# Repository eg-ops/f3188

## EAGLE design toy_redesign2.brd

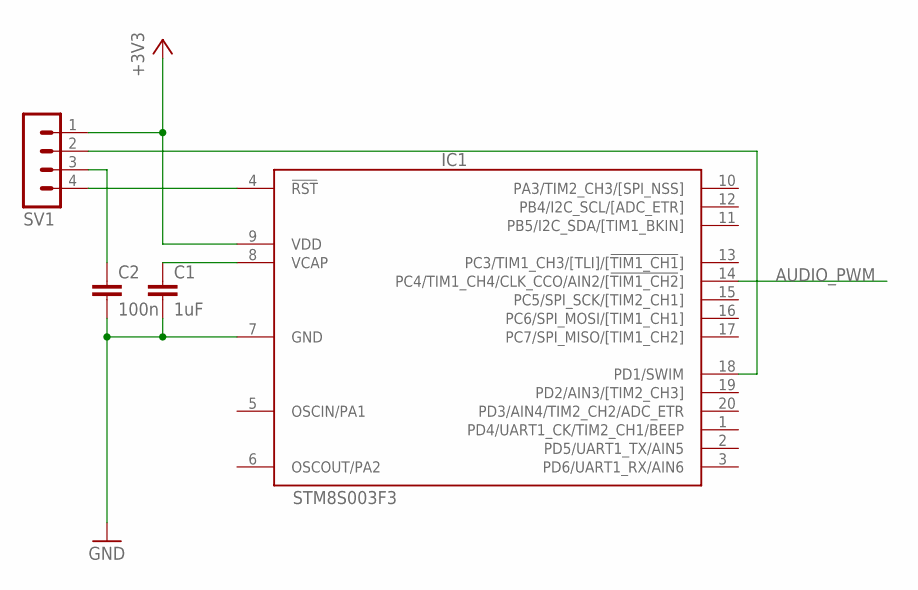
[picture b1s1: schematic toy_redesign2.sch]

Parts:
C1: 1uF; C0805
C2: 100n; C0805
IC1: STM8S003F3; TSSOP20
SV1: MA04-1

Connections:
+3V3: IC1.9 (VDD), SV1.1
AUDIO_PWM: IC1.14 (PC4/TIM1_CH4/CLK_CCO/AIN2/[!TIM1_CH2!])
GND: C1.2, C2.2, IC1.7 (GND)
unnamed: IC1.4 (!RST), SV1.4
unnamed: C1.1, IC1.8 (VCAP)
unnamed: C2.1, SV1.3
unnamed: IC1.18 (PD1/SWIM), SV1.2

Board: 2 copper layers, 4 parts (0 on the bottom side), 6 nets, no tracks yet.

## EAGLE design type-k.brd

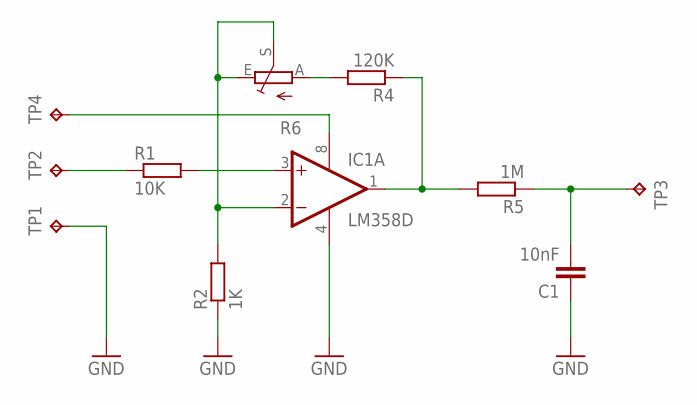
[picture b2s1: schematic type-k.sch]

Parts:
C1: 10nF; C0805
IC1: LM358D; SO08
R1: 10K; R0805
R2: 1K; R0805
R4: 120K; R0805
R5: 1M; R0805
R6: TRIM_EU-CA6V; CA6V
TP1, TP2, TP3, TP4: TPB2,54; B2,54

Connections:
GND: C1.1, IC1.4 (V-), R2.1, TP1.TP
unnamed: R1.1, TP2.TP
unnamed: IC1.3 (+IN), R1.2
unnamed: IC1.2 (-IN), R2.2, R6.E, R6.S
unnamed: R4.2, R6.A
unnamed: IC1.1 (OUT), R4.1, R5.2
unnamed: C1.2, R5.1, TP3.TP
unnamed: IC1.8 (V+), TP4.TP

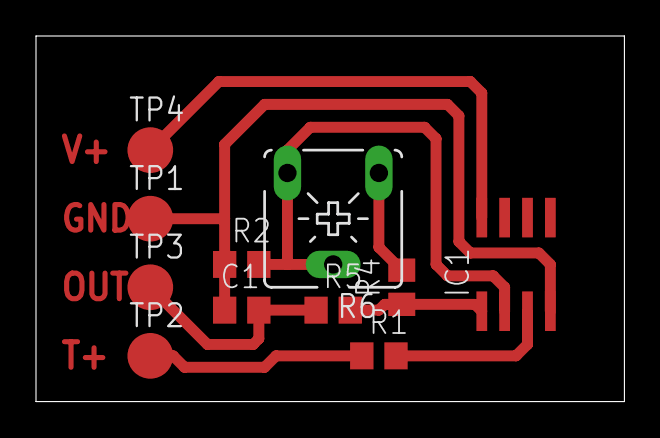
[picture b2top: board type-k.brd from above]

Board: 2 copper layers, 32.7 x 20.3 mm, 11 parts (0 on the bottom side), 8 nets.

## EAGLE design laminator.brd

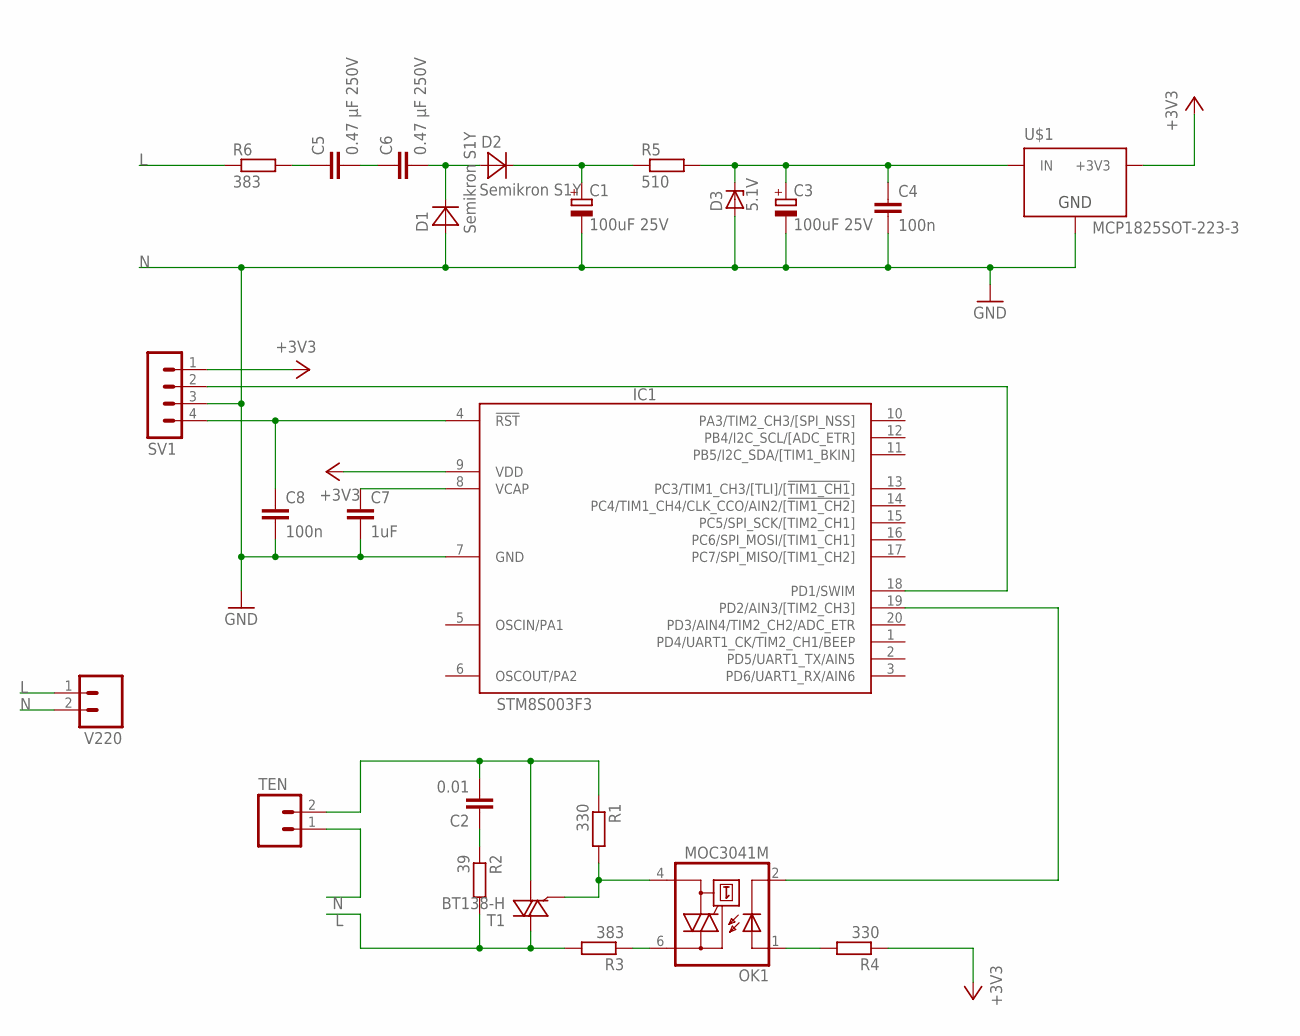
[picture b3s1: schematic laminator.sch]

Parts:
C1, C3: 100uF 25V; E2,5-6
C2: 0.01; C050-025X075
C4, C8: 100n; C0805
C5, C6: 0.47 µF 250V; C150-072X183
C7: 1uF; C0805
D1, D2: Semikron S1Y; SMA
D3: 5.1V; SMB
IC1: STM8S003F3; TSSOP20
OK1: MOC3041M; DIL06
R1: 330; 0207/7
R2: 39; 0207/7
R3, R6: 383; 0207/7
R4: 330; R1206
R5: 510; R0805
SV1: MA04-1
T1: BT138-H; TO220BH
TEN: M02; 02P
U$1: MCP1825SOT-223-3; SOT-223
V220: M02; 02P

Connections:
+3V3: IC1.9 (VDD), R4.1, SV1.1, U$1.3 (+3V3)
L: R2.2, R3.2, R6.1, T1.T2 (A2), V220.1
N: C1.-, C3.-, C4.2, C7.2, C8.2, D1.A, D3.A, IC1.7 (GND), SV1.3, TEN.1, U$1.2 (GND), V220.2
unnamed: OK1.6 (A2), R3.1
unnamed: C7.1, IC1.8 (VCAP)
unnamed: OK1.4 (A1), R1.2, T1.G
unnamed: C2.2, R1.1, T1.T1 (A1), TEN.2
unnamed: C6.2, D1.C, D2.A
unnamed: C2.1, R2.1
unnamed: C8.1, IC1.4 (!RST), SV1.4
unnamed: OK1.1 (A), R4.2
unnamed: IC1.18 (PD1/SWIM), SV1.2
unnamed: IC1.19 (PD2/AIN3/[TIM2_CH3]), OK1.2 (C)
unnamed: C1.+, D2.C, R5.1
unnamed: C3.+, C4.1, D3.C, R5.2, U$1.1 (IN)
unnamed: C5.1, R6.2
unnamed: C5.2, C6.1

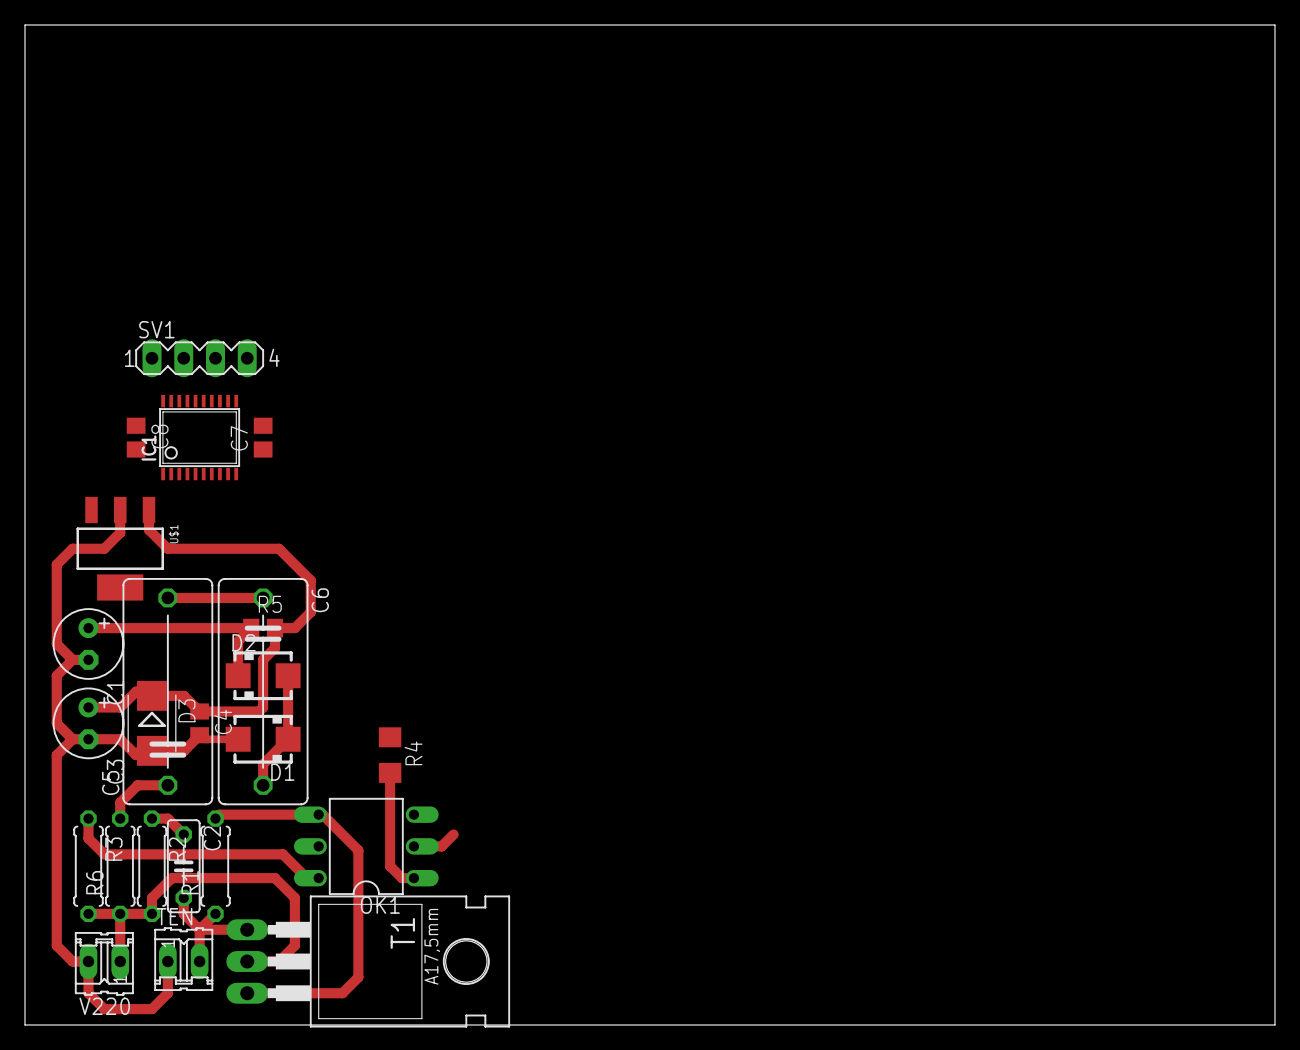
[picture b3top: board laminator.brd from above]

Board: 2 copper layers, 100.0 x 80.0 mm, 24 parts (0 on the bottom side), 17 nets.

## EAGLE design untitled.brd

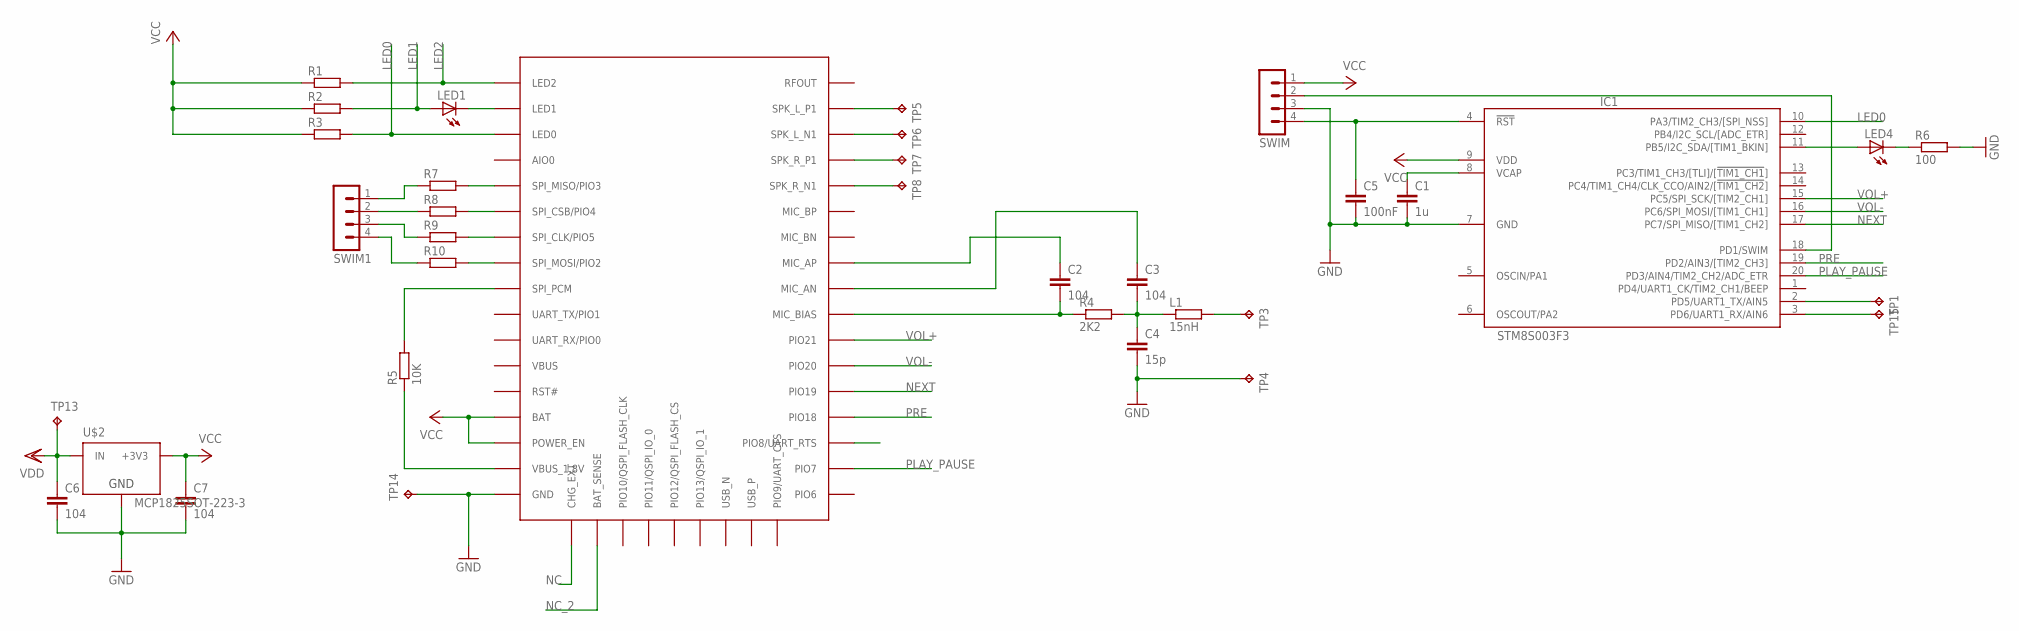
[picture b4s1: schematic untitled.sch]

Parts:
C1: 1u; C0805
C2, C3, C6, C7: 104; C0805
C4: 15p; C0805
C5: 100nF; C0805
IC1: STM8S003F3; TSSOP20
L1: 15nH; R0603
LED1, LED4: LEDCHIPLED_0603; CHIPLED_0603
R1, R2, R3, R7, R8, R9, R10: R-EU_R0805; R0805
R4: 2K2; R0805
R5: 10K; R0805
R6: 100; R0805
SWIM, SWIM1: MA04-1
TP1, TP3, TP4, TP5, TP6, TP7, TP8, TP13, TP14, TP15: TPB2,54; B2,54
U$1: F3188
U$2: MCP1825SOT-223-3; SOT-223

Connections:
GND: C1.2, C4.2, C5.2, C6.2, C7.2, IC1.7 (GND), R6.2, SWIM.3, TP4.TP, TP14.TP, U$1.P$17 (GND), U$2.2 (GND)
LED0: IC1.10 (PA3/TIM2_CH3/[SPI_NSS]), R3.2, U$1.P$3 (LED0)
LED1: LED1.A, R2.2
LED2: R1.2, U$1.P$1 (LED2)
unnamed: IC1.3 (PD6/UART1_RX/AIN6), TP15.TP
unnamed: IC1.2 (PD5/UART1_TX/AIN5), TP1.TP
unnamed: IC1.11 (PB5/I2C_SDA/[TIM1_BKIN]), LED4.A
unnamed: C2.2, R4.1, U$1.P$34 (MIC_BIAS)
unnamed: C3.2, C4.1, L1.1, R4.2
unnamed: C3.1, U$1.P$35 (MIC_AN)
unnamed: C2.1, U$1.P$36 (MIC_AP)
unnamed: L1.2, TP3.TP
unnamed: R5.1, U$1.P$16 (VBUS_1.8V)
unnamed: R5.2, U$1.P$9 (SPI_PCM)
unnamed: TP5.TP, U$1.P$42 (SPK_L_P1)
unnamed: TP6.TP, U$1.P$41 (SPK_L_N1)
unnamed: TP7.TP, U$1.P$40 (SPK_R_P1)
unnamed: TP8.TP, U$1.P$39 (SPK_R_N1)
unnamed: R7.2, U$1.P$5 (SPI_MISO/PIO3)
unnamed: R7.1, SWIM1.1
unnamed: R9.2, U$1.P$7 (SPI_CLK/PIO5)
unnamed: R8.1, SWIM1.2
unnamed: C1.1, IC1.8 (VCAP)
unnamed: C5.1, IC1.4 (!RST), SWIM.4
unnamed: IC1.18 (PD1/SWIM), SWIM.2
unnamed: LED4.C, R6.1
unnamed: R8.2, U$1.P$6 (SPI_CSB/PIO4)
unnamed: R9.1, SWIM1.3
unnamed: R10.2, U$1.P$8 (SPI_MOSI/PIO2)
unnamed: R10.1, SWIM1.4
unnamed: LED1.C, U$1.P$2 (LED1)
NC: U$1.P$18 (CHG_EXT)
NC_2: U$1.P$19 (BAT_SENSE)
NEXT: IC1.17 (PC7/SPI_MISO/[TIM1_CH2]), U$1.P$31 (PIO19)
PLAY_PAUSE: IC1.20 (PD3/AIN4/TIM2_CH2/ADC_ETR), U$1.P$28 (PIO7)
PRE: IC1.19 (PD2/AIN3/[TIM2_CH3]), U$1.P$30 (PIO18)
VBUS: U$1.P$12 (VBUS)
VCC: C7.1, IC1.9 (VDD), R1.1, R2.1, R3.1, SWIM.1, U$1.P$14 (BAT), U$1.P$15 (POWER_EN), U$2.3 (+3V3)
VDD: C6.1, TP13.TP, U$2.1 (IN)
VOL+: IC1.15 (PC5/SPI_SCK/[TIM2_CH1]), U$1.P$33 (PIO21)
VOL-: IC1.16 (PC6/SPI_MOSI/[TIM1_CH1]), U$1.P$32 (PIO20)

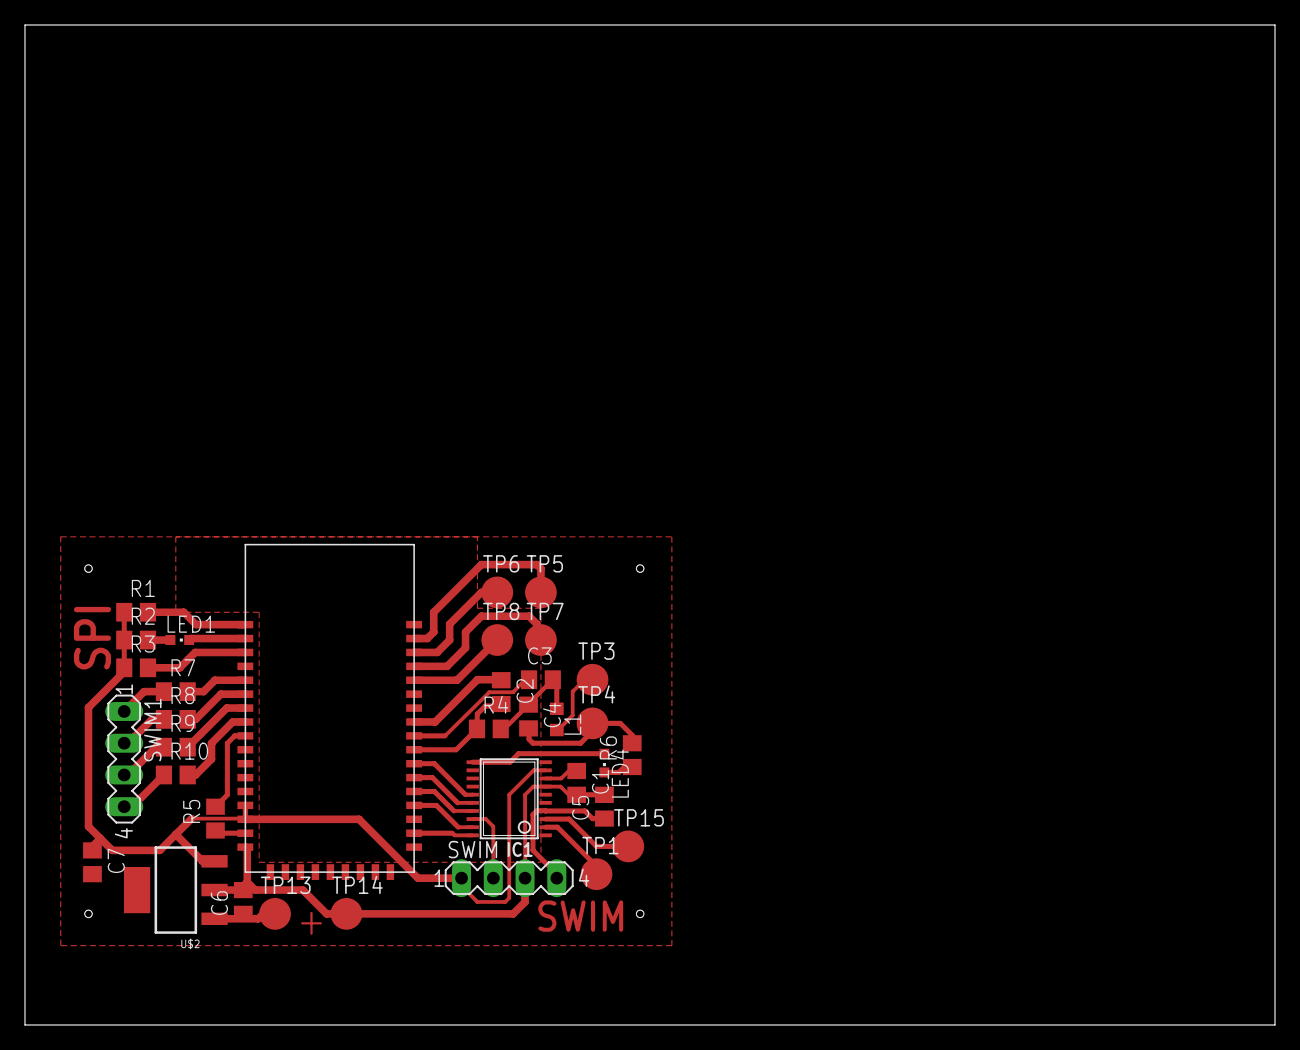
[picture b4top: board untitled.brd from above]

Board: 2 copper layers, 100.0 x 80.0 mm, 35 parts (0 on the bottom side), 38 nets.

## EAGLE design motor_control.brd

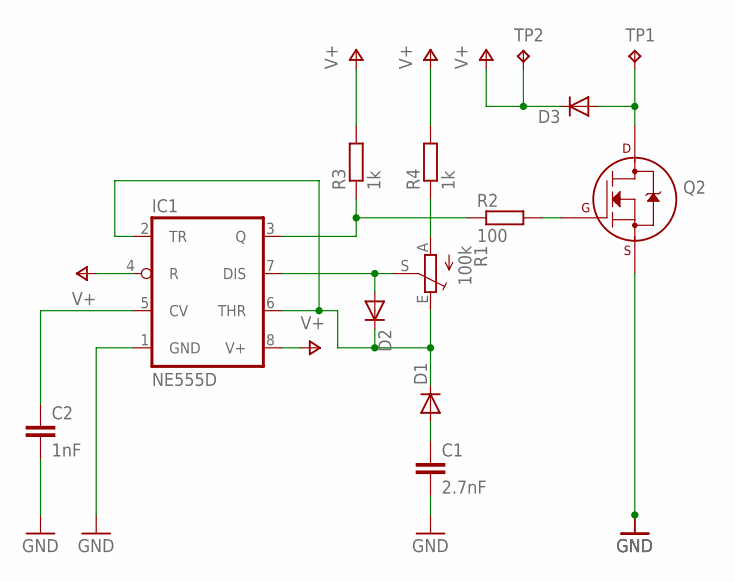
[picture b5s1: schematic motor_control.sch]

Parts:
C1: 2.7nF; C0805
C2: 1nF; C0805
D1, D2, D3: DIODE-SMB; SMB
IC1: NE555D; SO08
Q2: 2N7000_SOT23; SOT-23
R1: 100k; CA6V
R2: 100; R0805
R3, R4: 1k; R0805
TP1, TP2: TPB2,54; B2,54

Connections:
GND: C1.2, C2.2, IC1.1 (GND), Q2.2 (S)
unnamed: D1.C, D2.C, IC1.2 (TR), IC1.6 (THR), R1.E
unnamed: C2.1, IC1.5 (CV)
unnamed: D2.A, IC1.7 (DIS), R1.S
unnamed: Q2.1 (G), R2.2
unnamed: IC1.3 (Q), R2.1, R3.1
unnamed: D3.A, Q2.3 (D), TP1.TP
unnamed: C1.1, D1.A
unnamed: R1.A, R4.1
V+: D3.C, IC1.4 (R), IC1.8 (V+), R3.2, R4.2, TP2.TP

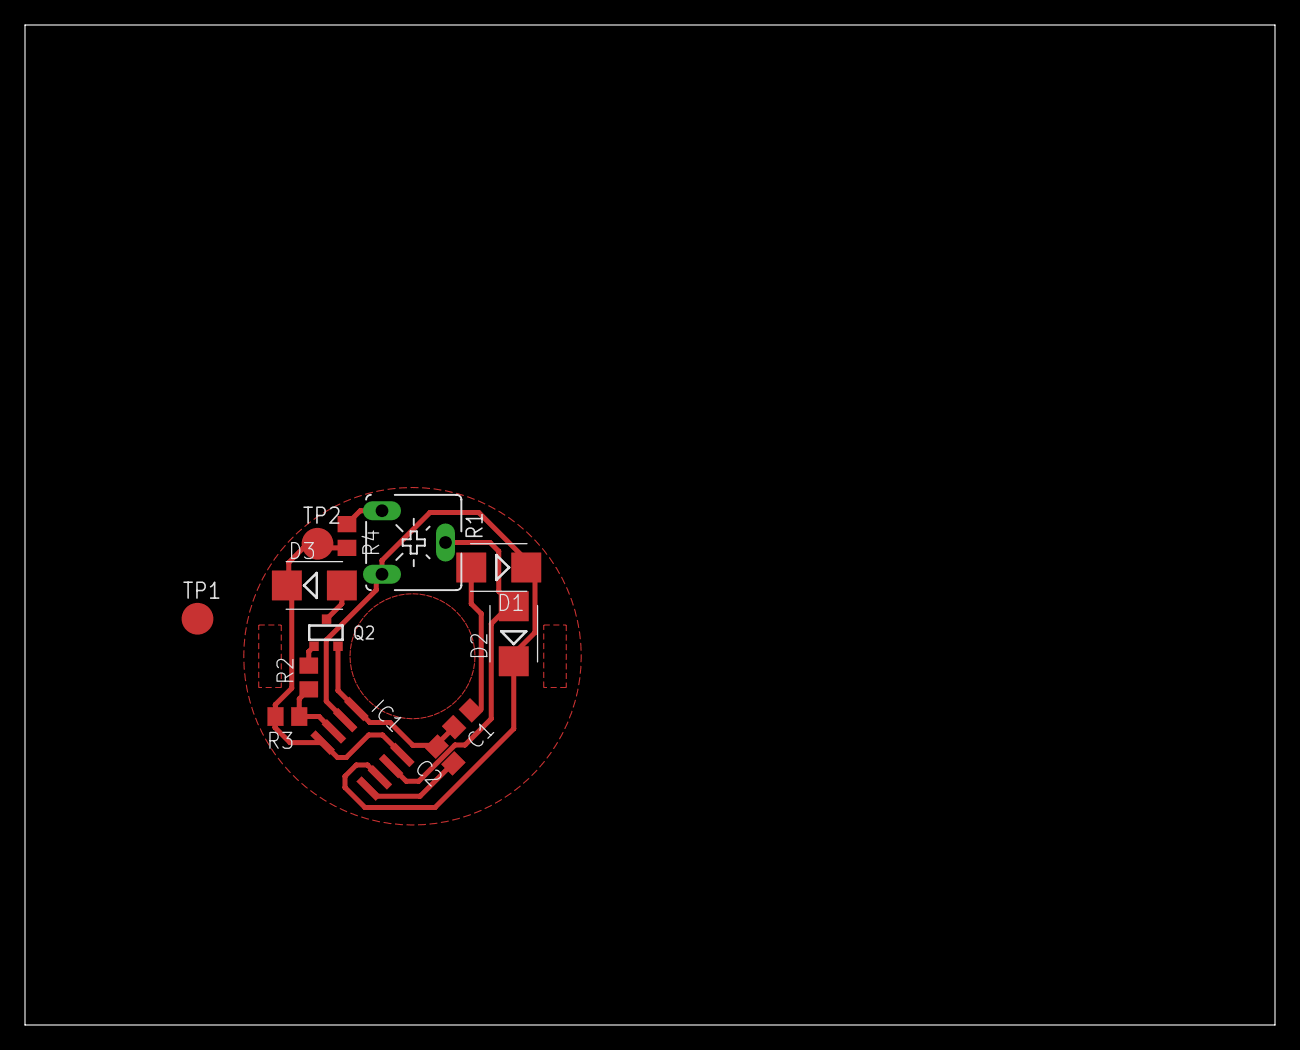
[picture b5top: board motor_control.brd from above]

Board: 2 copper layers, 100.0 x 80.0 mm, 13 parts (0 on the bottom side), 10 nets.

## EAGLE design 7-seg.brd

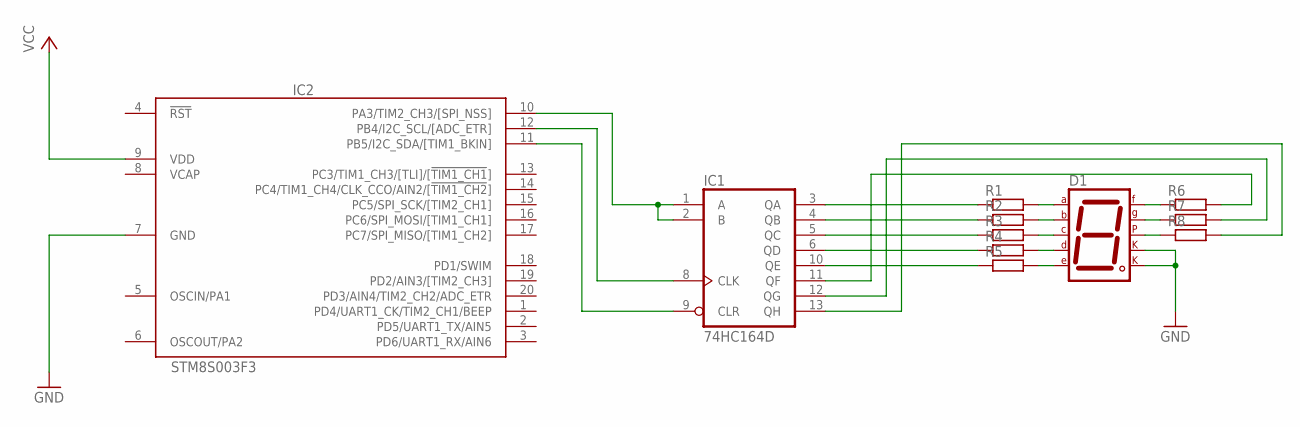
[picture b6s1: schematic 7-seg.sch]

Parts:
D1: 7SEG-MCK; 7SEG-7
IC1: 74HC164D; SO14
IC2: STM8S003F3; TSSOP20
R1, R2, R3, R4, R5, R6, R7, R8: R-EU_R0805; R0805

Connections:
GND: D1.1 (CK1), D1.6 (CK2), IC1.7 (GND), IC2.7 (GND)
unnamed: D1.10 (A), R1.2
unnamed: D1.9 (B), R2.2
unnamed: D1.8 (C), R3.2
unnamed: D1.5 (D), R4.2
unnamed: D1.4 (E), R5.2
unnamed: D1.2 (F), R6.1
unnamed: D1.3 (G), R7.1
unnamed: D1.7 (DP), R8.1
unnamed: IC1.3 (QA), R1.1
unnamed: IC1.4 (QB), R2.1
unnamed: IC1.5 (QC), R3.1
unnamed: IC1.6 (QD), R4.1
unnamed: IC1.10 (QE), R5.1
unnamed: IC1.11 (QF), R6.2
unnamed: IC1.12 (QG), R7.2
unnamed: IC1.13 (QH), R8.2
unnamed: IC1.1 (A), IC1.2 (B), IC2.10 (PA3/TIM2_CH3/[SPI_NSS])
unnamed: IC1.8 (CLK), IC2.12 (PB4/I2C_SCL/[ADC_ETR])
unnamed: IC1.9 (CLR), IC2.11 (PB5/I2C_SDA/[TIM1_BKIN])
VCAP: IC2.8 (VCAP)
VCC: IC1.14 (VCC), IC2.9 (VDD)

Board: 2 copper layers, 11 parts (1 on the bottom side), 21 nets, no tracks yet.

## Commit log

2015-08-07 second commit
2015-09-04 third commit
2015-09-11 removed leds
2015-09-15 motor_control
2015-09-15 small changes
2015-09-16 motor_layout first ver
2015-09-16 second try
2015-09-16 almost done
2015-09-16 small improve
2015-09-17 some changes
2015-09-17 added tx signal + led
2015-09-20 new design
2015-09-28 added laminator
2015-09-28 laminator board
2015-09-29 ac dc
2015-09-29 layout changes
2015-09-30 last version of laminator
2015-11-14 added type k
2016-12-19 Added STM32F042C6T6 in LQFP48 package
